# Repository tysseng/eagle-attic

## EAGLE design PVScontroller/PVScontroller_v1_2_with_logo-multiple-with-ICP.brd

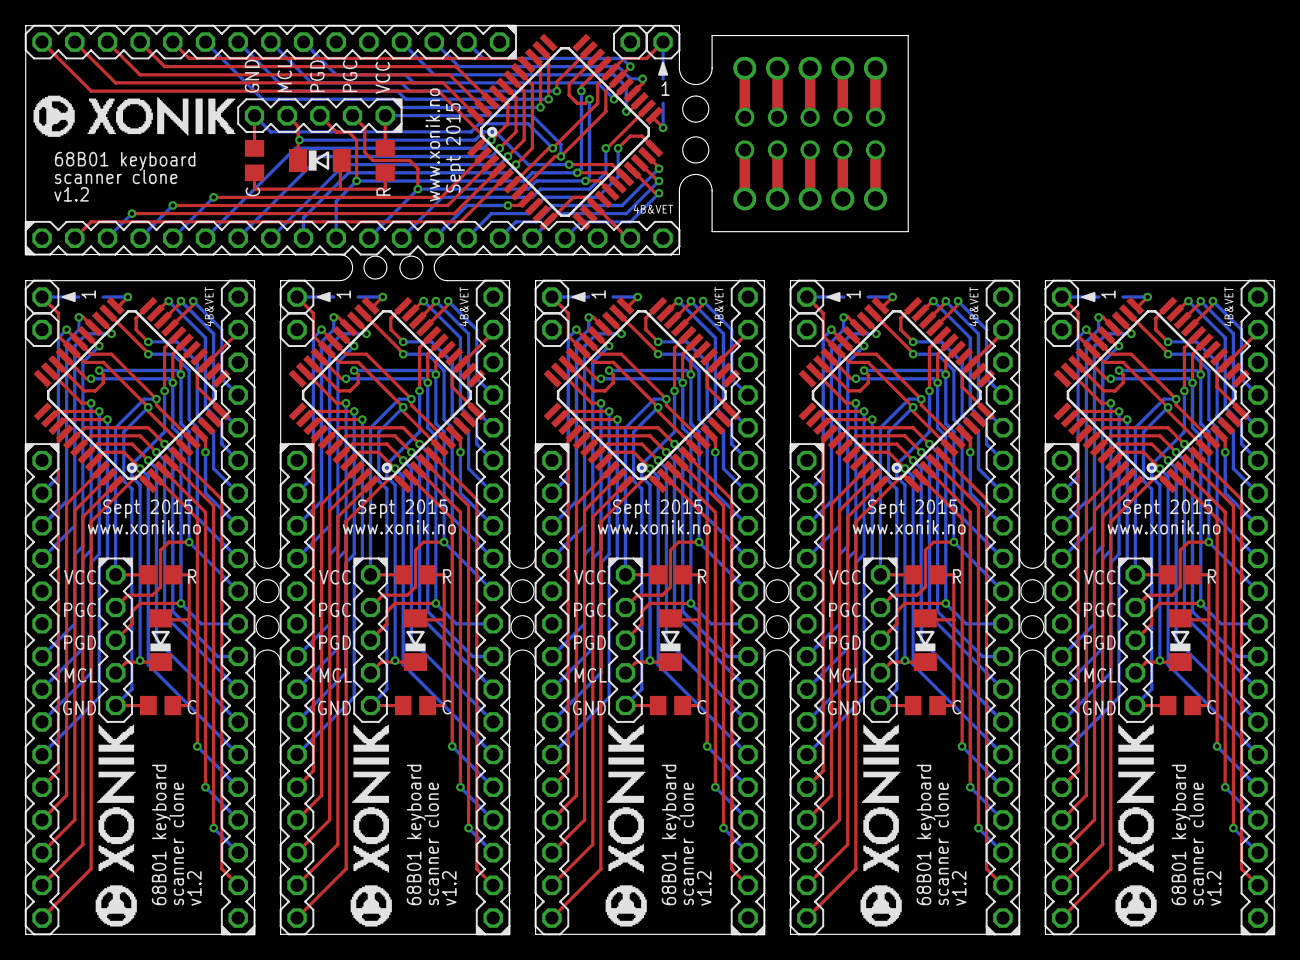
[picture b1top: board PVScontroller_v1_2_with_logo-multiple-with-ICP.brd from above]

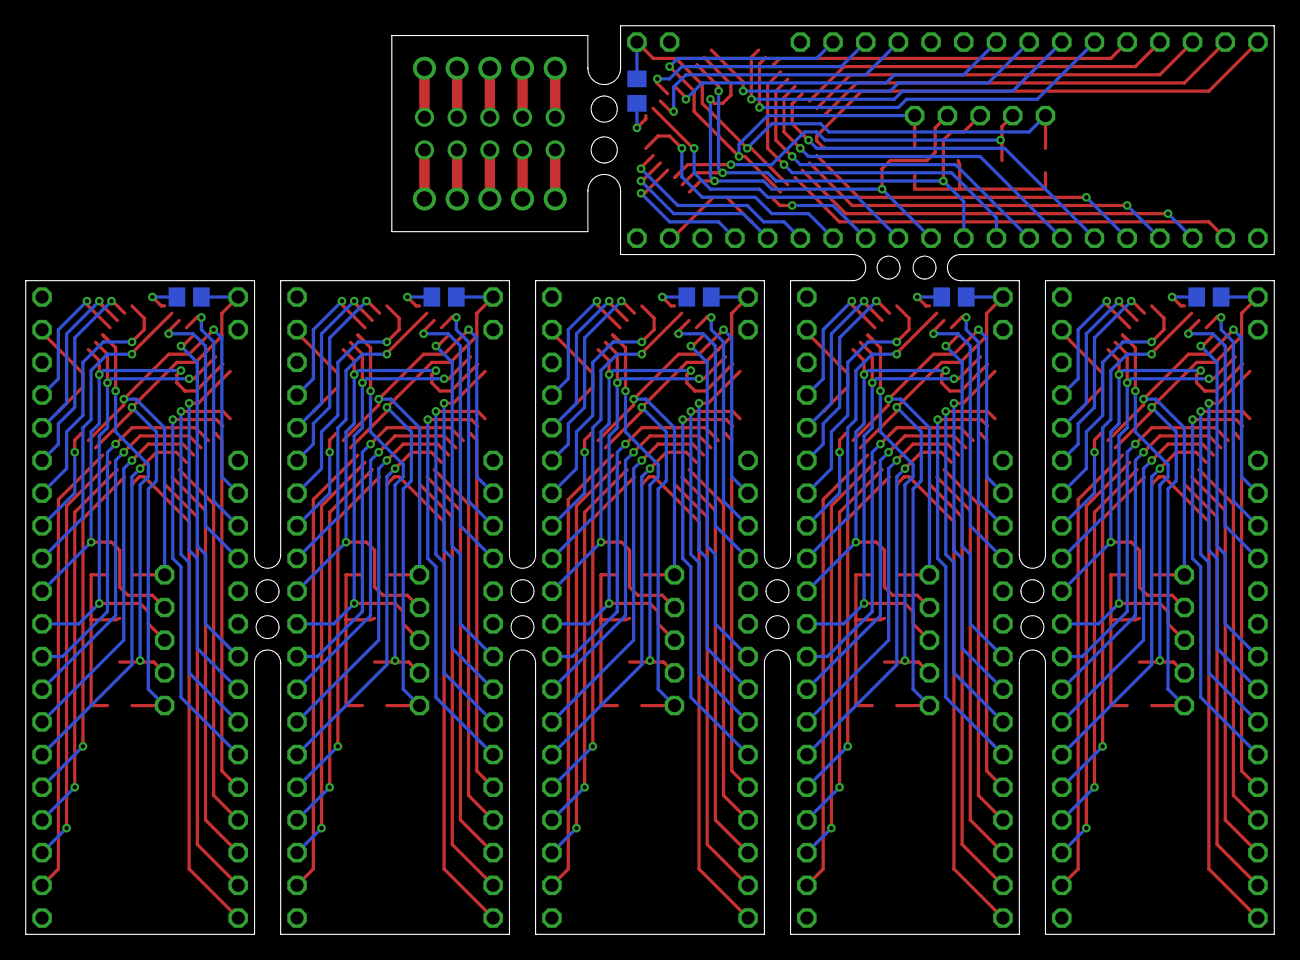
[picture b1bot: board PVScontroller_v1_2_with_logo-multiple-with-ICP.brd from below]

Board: 2 copper layers, 97.0 x 70.6 mm, 60 parts (6 on the bottom side), 198 nets.

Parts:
C, C1, C4, C6, C8, C10: 100nF; C0805
C2, C3, C5, C7, C9, C11: 10uF; C0805
D1, D2, D3, D4, D5, D6: SOD80C
IC1, IC2, IC3, IC4, IC5, IC6: PIC18F4455_TQFP; TQFP44
R, R1, R2, R3, R4, R5: 10k; R0805
SV1, SV3, SV5, SV8, SV11, SV13, SV16, SV18, SV21, SV23, SV26, SV28: MA01-1
SV2, SV10, SV15, SV20, SV25, SV30: MA20-1
SV4, SV7, SV12, SV17, SV22, SV27: MA05-1
SV6, SV9, SV14, SV19, SV24, SV29: MA15-1

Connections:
+5V: IC1.7, IC1.28, R.2, SV7.1, SV9.2
+5V1: IC2.7, IC2.28, R1.2, SV4.1, SV6.2
+5V2: IC3.7, IC3.28, R2.2, SV12.1, SV14.2
+5V3: IC4.7, IC4.28, R3.2, SV17.1, SV19.2
+5V4: IC5.7, IC5.28, R4.2, SV22.1, SV24.2
+5V5: IC6.7, IC6.28, R5.2, SV27.1, SV29.2
BS0: IC1.19, SV2.17
BS1: IC1.20, SV2.16
BS2: IC1.21, SV2.15
BS3: IC1.22, SV2.14
BS4: IC1.8, SV2.13
BS5: IC1.24, SV2.12
BS6: IC1.16, IC1.31, SV2.11, SV7.2
BS7: IC1.17, IC1.30, SV2.10, SV7.3
BS8: IC2.19, SV10.17
BS9: IC2.20, SV10.16
BS10: IC2.21, SV10.15
BS11: IC2.22, SV10.14
BS12: IC2.8, SV10.13
BS13: IC2.24, SV10.12
BS14: IC2.16, IC2.31, SV4.2, SV10.11
BS15: IC2.17, IC2.30, SV4.3, SV10.10
BS16: IC3.19, SV15.17
BS17: IC3.20, SV15.16
BS18: IC3.21, SV15.15
BS19: IC3.22, SV15.14
BS20: IC3.8, SV15.13
BS21: IC3.24, SV15.12
BS22: IC3.16, IC3.31, SV12.2, SV15.11
BS23: IC3.17, IC3.30, SV12.3, SV15.10
BS24: IC4.19, SV20.17
BS25: IC4.20, SV20.16
BS26: IC4.21, SV20.15
BS27: IC4.22, SV20.14
BS28: IC4.8, SV20.13
BS29: IC4.24, SV20.12
BS30: IC4.16, IC4.31, SV17.2, SV20.11
BS31: IC4.17, IC4.30, SV17.3, SV20.10
BS32: IC5.19, SV25.17
BS33: IC5.20, SV25.16
BS34: IC5.21, SV25.15
BS35: IC5.22, SV25.14
BS36: IC5.8, SV25.13
BS37: IC5.24, SV25.12
BS38: IC5.16, IC5.31, SV22.2, SV25.11
BS39: IC5.17, IC5.30, SV22.3, SV25.10
BS40: IC6.19, SV30.17
BS41: IC6.20, SV30.16
BS42: IC6.21, SV30.15
BS43: IC6.22, SV30.14
BS44: IC6.8, SV30.13
BS45: IC6.24, SV30.12
BS46: IC6.16, IC6.31, SV27.2, SV30.11
BS47: IC6.17, IC6.30, SV27.3, SV30.10
CARRY: IC1.25, SV9.4
CARRY1: IC2.25, SV6.4
CARRY2: IC3.25, SV14.4
CARRY3: IC4.25, SV19.4
CARRY4: IC5.25, SV24.4
CARRY5: IC6.25, SV29.4
CLK: IC1.26, SV9.3
CLK1: IC2.26, SV6.3
CLK2: IC3.26, SV14.3
CLK3: IC4.26, SV19.3
CLK4: IC5.26, SV24.3
CLK5: IC6.26, SV29.3
DB0: IC1.38, SV2.9
DB1: IC1.39, SV2.8
DB2: IC1.40, SV2.7
DB3: IC1.41, SV2.6
DB4: IC1.2, SV2.5
DB5: IC1.3, SV2.4
DB6: IC1.4, SV2.3
DB7: IC1.5, SV2.2
DB8: IC2.38, SV10.9
DB9: IC2.39, SV10.8
DB10: IC2.40, SV10.7
DB11: IC2.41, SV10.6
DB12: IC2.2, SV10.5
DB13: IC2.3, SV10.4
DB14: IC2.4, SV10.3
DB15: IC2.5, SV10.2
DB16: IC3.38, SV15.9
DB17: IC3.39, SV15.8
DB18: IC3.40, SV15.7
DB19: IC3.41, SV15.6
DB20: IC3.2, SV15.5
DB21: IC3.3, SV15.4
DB22: IC3.4, SV15.3
DB23: IC3.5, SV15.2
DB24: IC4.38, SV20.9
DB25: IC4.39, SV20.8
DB26: IC4.40, SV20.7
DB27: IC4.41, SV20.6
DB28: IC4.2, SV20.5
DB29: IC4.3, SV20.4
DB30: IC4.4, SV20.3
DB31: IC4.5, SV20.2
DB32: IC5.38, SV25.9
DB33: IC5.39, SV25.8
DB34: IC5.40, SV25.7
DB35: IC5.41, SV25.6
DB36: IC5.2, SV25.5
DB37: IC5.3, SV25.4
DB38: IC5.4, SV25.3
DB39: IC5.5, SV25.2
DB40: IC6.38, SV30.9
DB41: IC6.39, SV30.8
DB42: IC6.40, SV30.7
DB43: IC6.41, SV30.6
DB44: IC6.2, SV30.5
DB45: IC6.3, SV30.4
DB46: IC6.4, SV30.3
DB47: IC6.5, SV30.2
GND: C.1, C2.1, IC1.6, IC1.29, SV1.1, SV7.5
GND1: C1.1, C3.1, IC2.6, IC2.29, SV3.1, SV4.5
GND2: C4.1, C5.1, IC3.6, IC3.29, SV11.1, SV12.5
GND3: C6.1, C7.1, IC4.6, IC4.29, SV16.1, SV17.5
GND4: C8.1, C9.1, IC5.6, IC5.29, SV21.1, SV22.5
GND5: C10.1, C11.1, IC6.6, IC6.29, SV26.1, SV27.5
KYBD: IC1.11, IC1.14, SV2.19
KYBD1: IC2.11, IC2.14, SV10.19
KYBD2: IC3.11, IC3.14, SV15.19
KYBD3: IC4.11, IC4.14, SV20.19
KYBD4: IC5.11, IC5.14, SV25.19
KYBD5: IC6.11, IC6.14, SV30.19
KYINT: IC1.27, SV9.7
KYINT1: IC2.27, SV6.7
KYINT2: IC3.27, SV14.7
KYINT3: IC4.27, SV19.7
KYINT4: IC5.27, SV24.7
KYINT5: IC6.27, SV29.7
MCLR: D1.C, IC1.18, SV7.4
MCLR1: D2.C, IC2.18, SV4.4
MCLR2: D3.C, IC3.18, SV12.4
MCLR3: D4.C, IC4.18, SV17.4
MCLR4: D5.C, IC5.18, SV22.4
MCLR5: D6.C, IC6.18, SV27.4
unnamed: C1.2, D2.A, R1.1
unnamed: C4.2, D3.A, R2.1
unnamed: C6.2, D4.A, R3.1
unnamed: C.2, D1.A, R.1
unnamed: C8.2, D5.A, R4.1
unnamed: C10.2, D6.A, R5.1
TS0: IC1.32, SV9.8
TS1: IC1.35, SV9.9
TS2: IC1.36, SV9.10
TS3: IC1.37, SV9.11
TS4: IC1.42, SV9.12
TS5: IC1.43, SV9.13
TS6: IC1.44, SV9.14
TS7: IC1.1, SV9.15
TS8: IC2.32, SV6.8
TS9: IC2.35, SV6.9
TS10: IC2.36, SV6.10
TS11: IC2.37, SV6.11
TS12: IC2.42, SV6.12
TS13: IC2.43, SV6.13
TS14: IC2.44, SV6.14
TS15: IC2.1, SV6.15
TS16: IC3.32, SV14.8
TS17: IC3.35, SV14.9
TS18: IC3.36, SV14.10
TS19: IC3.37, SV14.11
TS20: IC3.42, SV14.12
TS21: IC3.43, SV14.13
TS22: IC3.44, SV14.14
TS23: IC3.1, SV14.15
TS24: IC4.32, SV19.8
TS25: IC4.35, SV19.9
TS26: IC4.36, SV19.10
TS27: IC4.37, SV19.11
TS28: IC4.42, SV19.12
TS29: IC4.43, SV19.13
TS30: IC4.44, SV19.14
TS31: IC4.1, SV19.15
TS32: IC5.32, SV24.8
TS33: IC5.35, SV24.9
TS34: IC5.36, SV24.10
TS35: IC5.37, SV24.11
TS36: IC5.42, SV24.12
TS37: IC5.43, SV24.13
TS38: IC5.44, SV24.14
TS39: IC5.1, SV24.15
TS40: IC6.32, SV29.8
TS41: IC6.35, SV29.9
TS42: IC6.36, SV29.10
TS43: IC6.37, SV29.11
TS44: IC6.42, SV29.12
TS45: IC6.43, SV29.13
TS46: IC6.44, SV29.14
TS47: IC6.1, SV29.15
VDD_CORE: C2.2, IC1.23
VDD_CORE1: C3.2, IC2.23
VDD_CORE2: C5.2, IC3.23
VDD_CORE3: C7.2, IC4.23
VDD_CORE4: C9.2, IC5.23
VDD_CORE5: C11.2, IC6.23
